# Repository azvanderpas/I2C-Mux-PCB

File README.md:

# I2C-Mux-PCB
PCA9548A I2C mux breakout board in KiCad

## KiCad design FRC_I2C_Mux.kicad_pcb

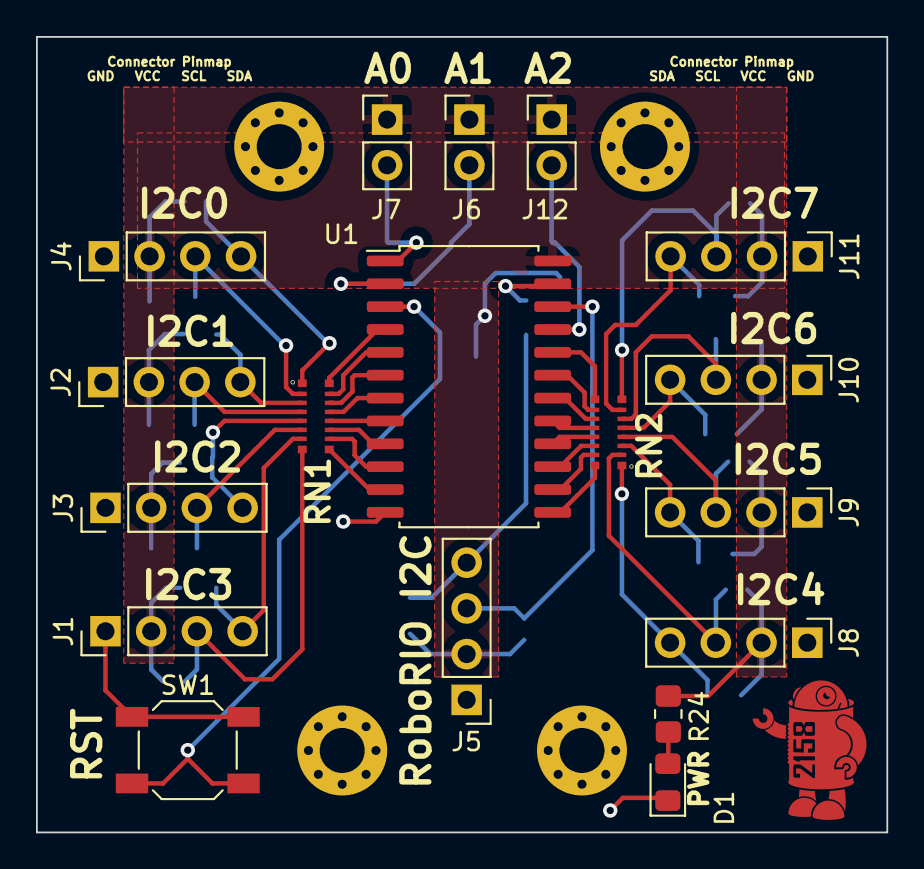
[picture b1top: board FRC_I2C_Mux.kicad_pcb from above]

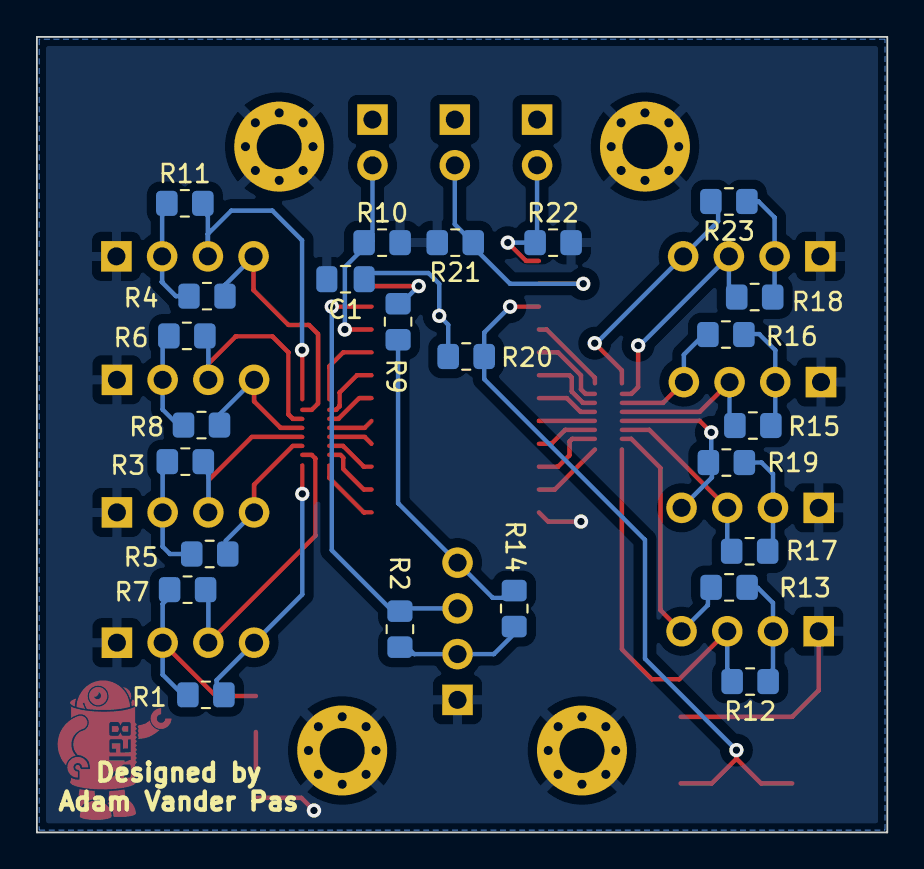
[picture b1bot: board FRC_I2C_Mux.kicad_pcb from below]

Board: 2 copper layers, 47.2 x 44.2 mm, 46 parts (24 on the bottom side), 42 nets.

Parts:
C1: C; C_0805_2012Metric_Pad1.18x1.45mm_HandSolder
D1: LED; LED_0805_2012Metric_Pad1.15x1.40mm_HandSolder
J1, J2, J3, J4, J5, J8, J9, J10, J11: Conn_01x04; PinHeader_1x04_P2.54mm_Vertical
J6, J7, J12: Conn_01x02; PinHeader_1x02_P2.54mm_Vertical
R1, R3, R4, R5, R6, R7, R8, R10, R11, R12, R13, R15, R16, R17, R18, R19, R20, R21, R22, R23: 20k; R_0805_2012Metric_Pad1.20x1.40mm_HandSolder
R2, R14: 1k; R_0805_2012Metric_Pad1.20x1.40mm_HandSolder
R9, R24: 33; R_0805_2012Metric_Pad1.20x1.40mm_HandSolder
REF1, REF2, REF3, REF4: MountingHole_Pad; MountingHole_2.5mm_Pad_Via
RN1, RN2: R_Pack08; EXB2HV_1
SW1: SW_Push; SW_SPST_SKQG_WithStem
U1: PCA9548ADW; SOIC-24W_7.5x15.4mm_P1.27mm

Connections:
+3V3: C1.1, J1.2, J2.2, J3.2, J4.2, J5.2, J6.1, J7.1, J8.2, J9.2, J10.2, J11.2, J12.1, R1.1, R2.1, R3.1, R4.1, R5.1, R6.1, R7.1, R8.1, R11.1, R12.1, R13.1, R14.1, R15.1, R16.1, R17.1, R18.1, R19.1, R20.1, R23.1, R24.2, U1.24 (VCC)
/A0: J7.2, R22.1, U1.1 (A0)
/A1: J6.2, R21.1, U1.2 (A1)
/A2: J12.2, R10.1, U1.21 (A2)
/SCL: J5.3, R2.2, U1.22 (SCL)
/SCL0: J4.3, R18.2, RN1.2 (R2.1)
/SCL1: J2.3, R15.2, RN1.4 (R4.1)
/SCL2: J3.3, R17.2, RN1.6 (R6.1)
/SCL3: J1.3, R12.2, RN1.8 (R8.1)
/SCL4: J8.3, R7.2, RN2.2 (R2.1)
/SCL5: J9.3, R3.2, RN2.4 (R4.1)
/SCL6: J10.3, R6.2, RN2.6 (R6.1)
/SCL7: J11.3, R11.2, RN2.8 (R8.1)
/SDA: J5.4, R9.1, R14.2
/SDA0: J4.4, R23.2, RN1.1 (R1.1)
/SDA1: J2.4, R16.2, RN1.3 (R3.1)
/SDA2: J3.4, R19.2, RN1.5 (R5.1)
/SDA3: J1.4, R13.2, RN1.7 (R7.1)
/SDA4: J8.4, R1.2, RN2.1 (R1.1)
/SDA5: J9.4, R5.2, RN2.3 (R3.1)
/SDA6: J10.4, R8.2, RN2.5 (R5.1)
/SDA7: J11.4, R4.2, RN2.7 (R7.1)
GND: C1.2, D1.1 (K), J1.1, J2.1, J3.1, J4.1, J5.1, J8.1, J9.1, J10.1, J11.1, R10.2, R21.2, R22.2, REF1.1, REF2.1, REF3.1, REF4.1, SW1.1, U1.12 (GND)
unnamed: D1.2 (A), R24.1
unnamed: R9.2, U1.23 (SDA)
unnamed: R20.2, SW1.2, U1.3 (~RESET)
unnamed: RN1.9 (R8.2), U1.11 (SC3)
unnamed: RN1.10 (R7.2), U1.10 (SD3)
unnamed: RN1.11 (R6.2), U1.9 (SC2)
unnamed: RN1.12 (R5.2), U1.8 (SD2)
unnamed: RN1.13 (R4.2), U1.7 (SC1)
unnamed: RN1.14 (R3.2), U1.6 (SD1)
unnamed: RN1.15 (R2.2), U1.5 (SC0)
unnamed: RN1.16 (R1.2), U1.4 (SD0)
unnamed: RN2.9 (R8.2), U1.20 (SC7)
unnamed: RN2.10 (R7.2), U1.19 (SD7)
unnamed: RN2.11 (R6.2), U1.18 (SC6)
unnamed: RN2.12 (R5.2), U1.17 (SD6)
unnamed: RN2.13 (R4.2), U1.16 (SC5)
unnamed: RN2.14 (R3.2), U1.15 (SD5)
unnamed: RN2.15 (R2.2), U1.14 (SC4)
unnamed: RN2.16 (R1.2), U1.13 (SD4)

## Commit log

2022-03-08 add footprints to library
2022-03-08 Remap footprints and update gitignore
2022-03-13 Remove footprints that are in common library
    Remove/ignore kicad_prl file
    add local footprint library
2022-03-13 Fix footprint paths
2022-03-13 Update resistors to 0805s
2022-03-13 Replace LED with 0805
2022-03-14 Add mouser links to BoM
2023-09-01 Fix kibot
2023-09-01 Codespaces config
2023-09-01 YES!
2023-09-01 YESgit stage .devcontainer/*
2023-09-01 YESSS!
2023-09-01 YESSSS!
